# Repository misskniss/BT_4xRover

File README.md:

# BT_4xRover
4-Wheel Drive small Rover Bot. Bluetooth (HC-05) &amp; Acceleromter Controlled via Samsung Galaxy S5 Running SensoDuino App (Android 4.4.2). 

[Watch the video](https://drive.google.com/a/setek.io/file/d/0B9k3eDZYhuLoRUtQbXJCNnFkb2M/view) of the final product completeing a test course.

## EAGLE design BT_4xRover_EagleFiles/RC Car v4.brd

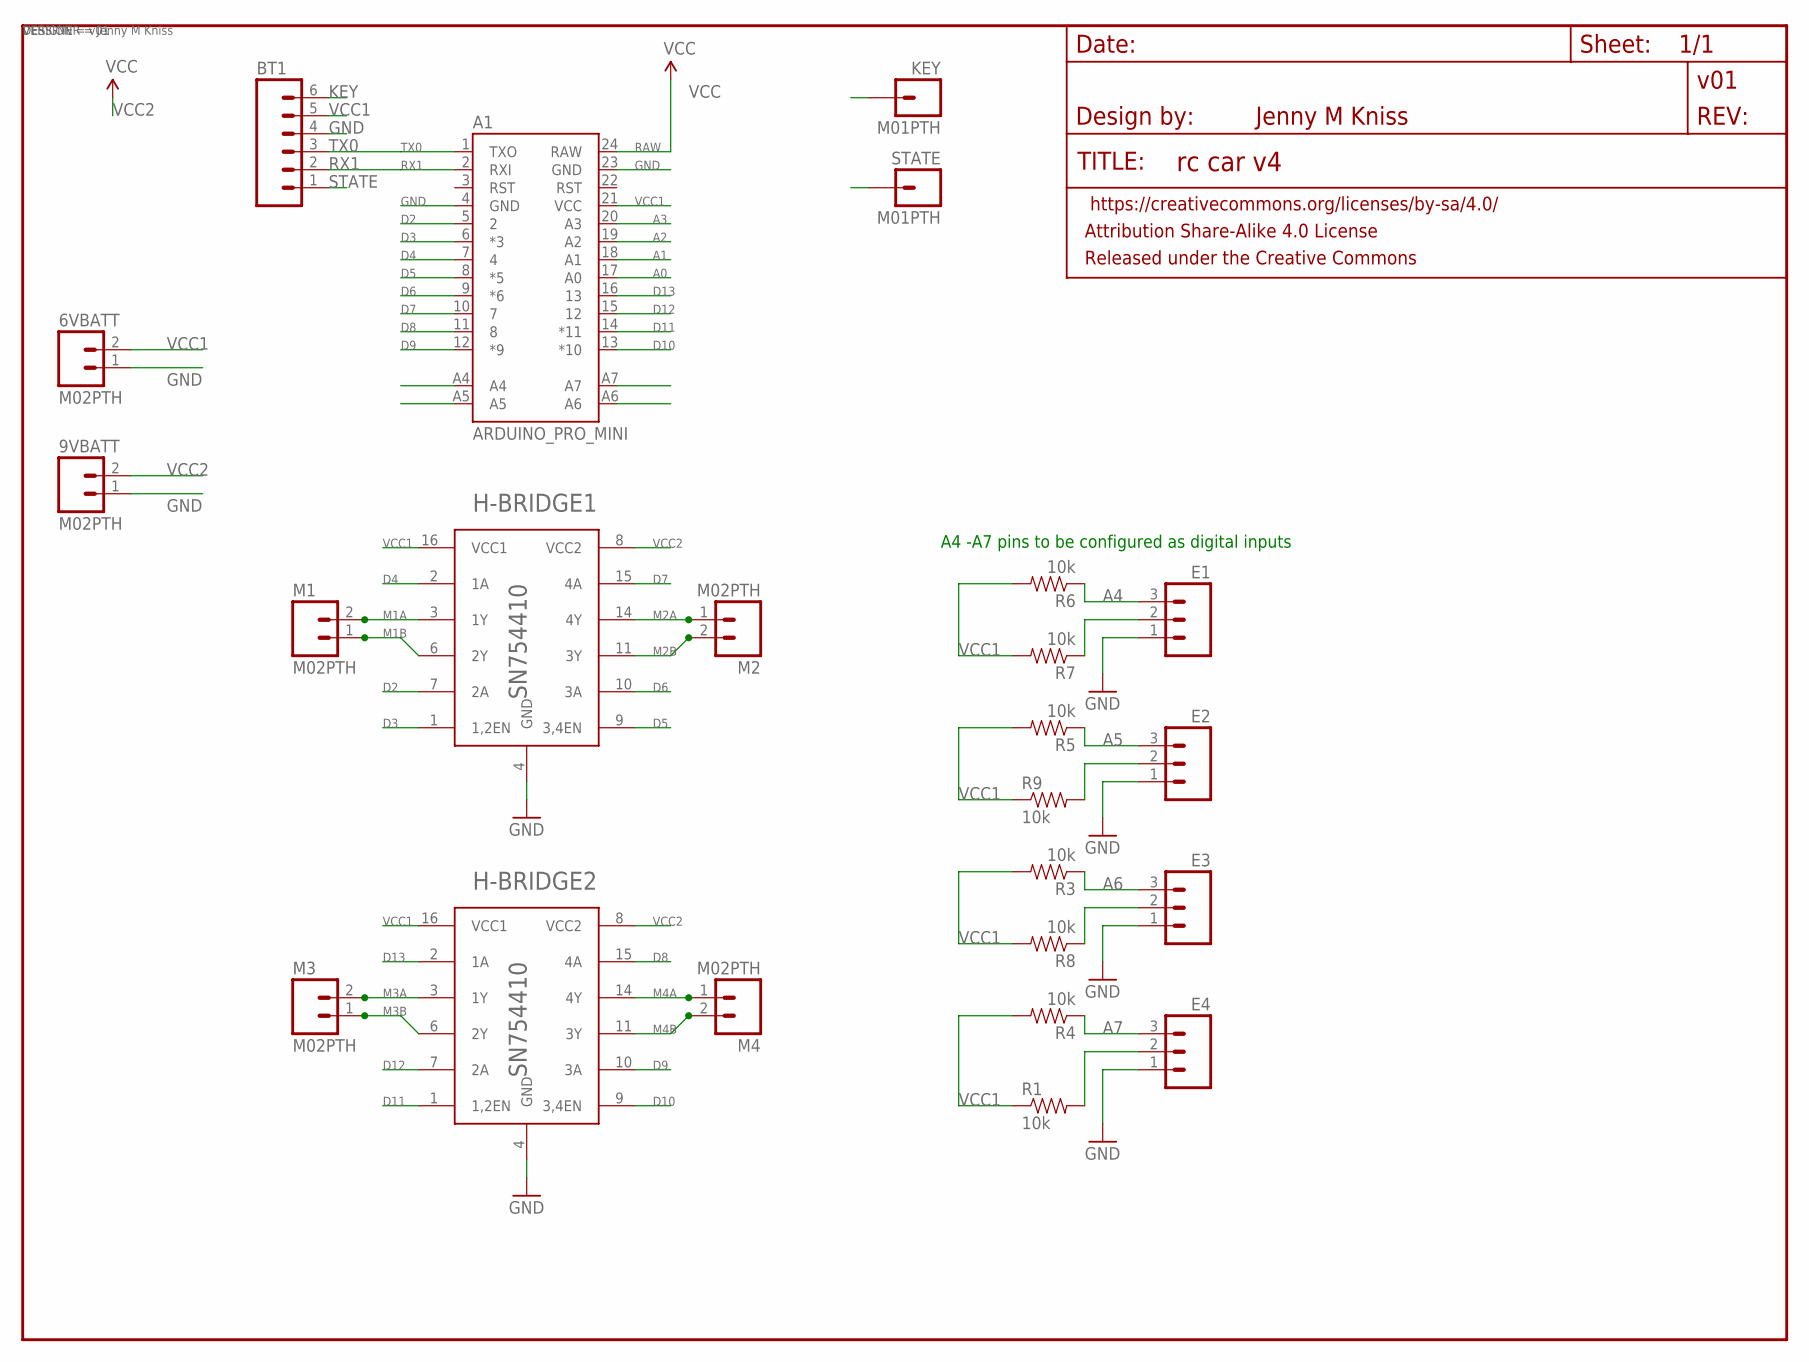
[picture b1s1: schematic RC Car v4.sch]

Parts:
6VBATT, 9VBATT: M02PTH; 1X02
A1: ARDUINO_PRO_MINI
BT1: M06SILK_FEMALE_PTH; 1X06
E1, E2, E3, E4: M03PTH; 1X03
H-BRIDGE1, H-BRIDGE2: SN754410; DIL16
KEY: M01PTH; 1X01
M1, M2, M3, M4: M02PTH; 1X02
R1, R3, R4, R5, R6, R7, R8, R9: 10k; AXIAL-0.3
RC_CAR: JENNY M KNISS; CREATIVE_COMMONS
STATE: M01PTH; 1X01

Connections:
A0: A1.17 (A0)
A1: A1.18 (A1)
A2: A1.19 (A2)
A3: A1.20 (A3)
A4: A1.A4, E1.3, R6.P$1 (1)
A5: A1.A5, E2.3, R5.P$1 (1)
A6: A1.A6, E3.3, R3.P$1 (1)
A7: A1.A7, E4.3, R4.P$1 (1)
D2: A1.5 (2), H-BRIDGE1.7 (2A)
D3: A1.6 (*3), H-BRIDGE1.1 (1,2EN)
D4: A1.7 (4), H-BRIDGE1.2 (1A)
D5: A1.8 (*5), H-BRIDGE1.9 (3,4EN)
D6: A1.9 (*6), H-BRIDGE1.10 (3A)
D7: A1.10 (7), H-BRIDGE1.15 (4A)
D8: A1.11 (8), H-BRIDGE2.15 (4A)
D9: A1.12 (*9), H-BRIDGE2.10 (3A)
D10: A1.13 (*10), H-BRIDGE2.9 (3,4EN)
D11: A1.14 (*11), H-BRIDGE2.1 (1,2EN)
D12: A1.15 (12), H-BRIDGE2.7 (2A)
D13: A1.16 (13), H-BRIDGE2.2 (1A)
GND: 6VBATT.1, 9VBATT.1, A1.4 (GND), A1.23 (GND), BT1.4, E1.1, E2.1, E3.1, E4.1, H-BRIDGE1.4 (GND), H-BRIDGE1.5 (GND), H-BRIDGE1.12 (GND), H-BRIDGE1.13 (GND), H-BRIDGE2.4 (GND), H-BRIDGE2.5 (GND), H-BRIDGE2.12 (GND), H-BRIDGE2.13 (GND)
KEY: BT1.6, KEY.1
M1A: H-BRIDGE1.3 (1Y), M1.2
M1B: H-BRIDGE1.6 (2Y), M1.1
M2A: H-BRIDGE1.14 (4Y), M2.1
M2B: H-BRIDGE1.11 (3Y), M2.2
M3A: H-BRIDGE2.3 (1Y), M3.2
M3B: H-BRIDGE2.6 (2Y), M3.1
M4A: H-BRIDGE2.14 (4Y), M4.1
M4B: H-BRIDGE2.11 (3Y), M4.2
unnamed: E2.2, R9.P$2 (2)
unnamed: E1.2, R7.P$1 (1)
unnamed: E3.2, R8.P$1 (1)
unnamed: E4.2, R1.P$2 (2)
RAW: A1.24 (RAW)
RX1: A1.2 (RXI), BT1.2
STATE: BT1.1, STATE.1
TX0: A1.1 (TXO), BT1.3
VCC1: 6VBATT.2, A1.21 (VCC), BT1.5, H-BRIDGE1.16 (VCC1), H-BRIDGE2.16 (VCC1), R1.P$1 (1), R3.P$2 (2), R4.P$2 (2), R5.P$2 (2), R6.P$2 (2), R7.P$2 (2), R8.P$2 (2), R9.P$1 (1)
VCC2: 9VBATT.2, H-BRIDGE1.8 (VCC2), H-BRIDGE2.8 (VCC2)

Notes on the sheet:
A4 -A7 pins to be configured as digital inputs

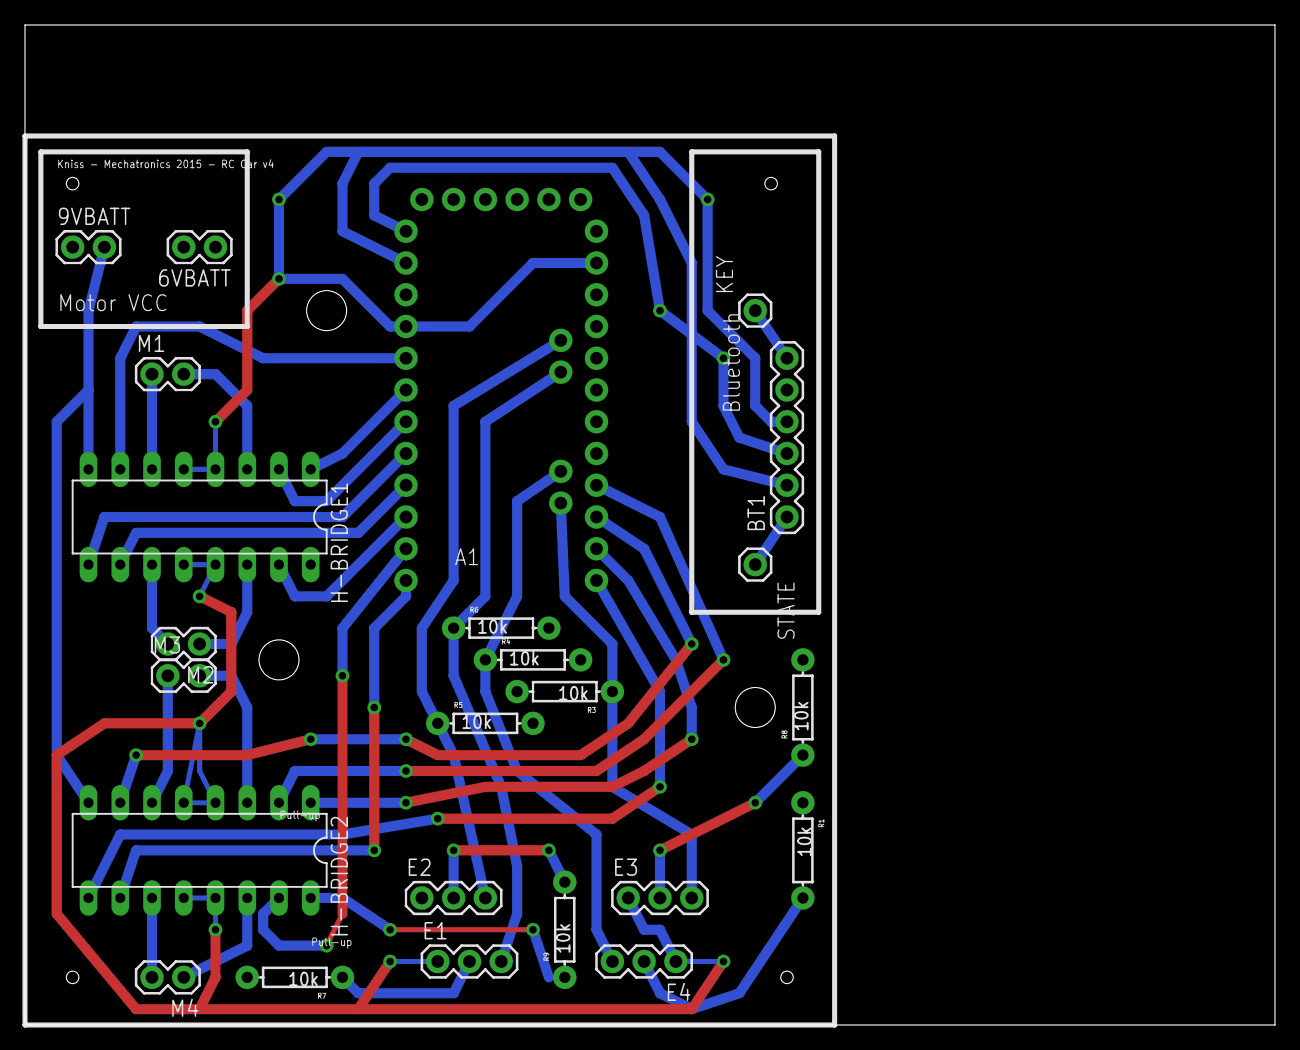
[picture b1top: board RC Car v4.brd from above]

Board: 2 copper layers, 100.0 x 80.0 mm, 25 parts (0 on the bottom side), 35 nets.

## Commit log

2015-06-23 Initial Commit of BT_4xRover files.
2015-06-23 Adding link to video of the BT_4xRover
2015-11-14 Example for a "using git" in DBS Reasearch

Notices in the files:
parts and their libraries:
SparkFun-Connectors: Licensing: Creative Commons ShareAlike 4.0 International - https://creativecommons.org/licenses/by-sa/4.0
SparkFun-Aesthetics: Released under the Creative Commons Attribution Share-Alike 4.0 License
SparkFun-Aesthetics: https://creativecommons.org/licenses/by-sa/4.0
